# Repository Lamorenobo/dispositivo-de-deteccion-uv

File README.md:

# Dispositivo de detección uv
Nuestro dispositivo detecta la rediacion uv, y envia esta señal a una app en la cual dependiendo de el rango de  la radiacion se muestran las prevenciones que hay que tener para prevenir afectaciones por rayos UV
## Introducción
Nuestro proyecto consiste en un dispositivo capaz de detectar la radiacion UV, el cual envia unas señales al microcontrolador(ESP-32, programado en C), y dependiendo el rango de intensidad de radiacion UV, se encarga de prender o apagar unos leds en el dispositivo los cuales  indican la peligrosidad de la radiacion en ese momento especifico. Paralelamente a esto,mediante la conexion Bluetooth entre el esp 32 y el celular, se le indica al usario las prevenciones que deberia tomar de acuerdo al indice de radiación UV que este indicando el microcontrolador, todo esto a travez de una aplicacion programada en app inventor.
## ¿Porque?
Despues de realizar un analisis profundo al clima de la ciudad de Bogota, nos dimos cuenta que la radiacion UV durante el día, se mantiene en indices que se  consideran perjudicales para la piel.Ademas es importante mencionar que segun datos de la liga Colombiana contra el cancer y el INC Bogota es una de las ciudades con mas incidencia en casos de cancer de piel, y es aca donde nos dimos cuenta que estos dos datos estan correlacionados por lo cual nos pareció indispensable crear un dispositivo que avise en todo momento a los bogotanos sobre la radiacion UV que  se presenta al instante, y las precauciones que deberian tomar.
# Objetivo General
Desarrolar un Dispositivo que mediante la lectura del ESP-32 de los datos recogidos por el sensor UV, prenda determiando led indicando la intensidad de radiación UV en tiempo real y por conexión Wi-Fi enviar esta información a un aplicativo movil.
## Objetivos específicos
- Programar el microcontrolador y configurar la conectividad Wi-Fi
- Programar una aplicación que indique al usuario las precauciones que debería tomar, dependiendo la intensidad de radiacion UV en tiempo real
- Hacer en KICAD el Diseño de la placa (PCB) en la cual van a ir montados los componentes
- Hacer las respectivas pruebas del artefacto
- Documentar el proceso de creacion
# Materiales
- ESP-32
- Modulo de Carga MH18650
- Portabateria 18650
- Sensor UV Guva-s12sd
- 5 resistencias de 330 Ohmios
- 1 resistencia de 1KiloOhm
- Placa de Circuito (PCB)
- Materiales para soldar
- Bateria 9V
- 5 Leds
# Proceso Creativo
Empezariamos, como es debido en todo proceso de creacion tecnologico, con el diagrama de caja negra y el esquema del circuito:

## Diagrama de cajas negras

## Esquema del circuito 
A continuación presentamos el circuito  del dispositivo de detección UV elaborado en kicad.

## Programacion del ESP-32 (Micropython)
[codigo esp32 micropython (1).txt](https://github.com/Lamorenobo/dispositivo-de-deteccion-uv/files/13405623/codigo.esp32.micropython.1.txt)

## Version (Protoboard)
Tras tener la programacion del microcrontolador y el esquema del circuito, procedimos a pasarlo todo a una protoboard y comprobar el funcionamiento de todo el dispositivo<br>
 <br>
 <br>
<br>

En esas fotos se puede apreciar nuestra felicidad al percaarnos que el ESP-32 estaba haciendo su trabajo a la perfeccion, encendiendo y apagando Leds, dependiendo a la radiacion UV que fuera expuesto el SENSOR, ya solo faltaba empezar a crear la aplicacion
## Capitulo:PCB
Sin embargo debido a errores grupales no contabamos con que el proyecto debia realizarse sobre una PCB, por lo cual empezamos a documentarnos sobre el uso de la herramienta KICAD y las 
 librerias necesarias para armar el Esquema de la PCB para posteriormente mandarla a fabricar
###  Primera Version de la PCB:(Error)<br>
<br>
<br>

### PCB FINAL:

### Componentes en la PCB.....
Despues de tener Todos los materiales necesarios, nos vimos ante el reto de la soldadura puesto que ninguno tenia la experticia ni la tecnica para esta, sin embargo tras dedicarle bastante y con ayuda del profesor Johnny, logramos soldar todos los componenetes del dispositivo de manera correcta en la PCB:

#### Soldadura:

Dispositivo Final:

# Prueba ¿Final?:
Tras el armado del Dispositivo fisico procedimos a probarlo, y tras un primer fallo debido a un error de digitalizacion de un pin en el codigo, no obtuvimos el resultado esperado, sin embargo despues de corregir este error, obtuvimos lo que queriamos:

https://github.com/Lamorenobo/dispositivo-de-deteccion-uv/assets/142939223/29cb111f-80ca-4eb9-bf07-753b7d6bfc69

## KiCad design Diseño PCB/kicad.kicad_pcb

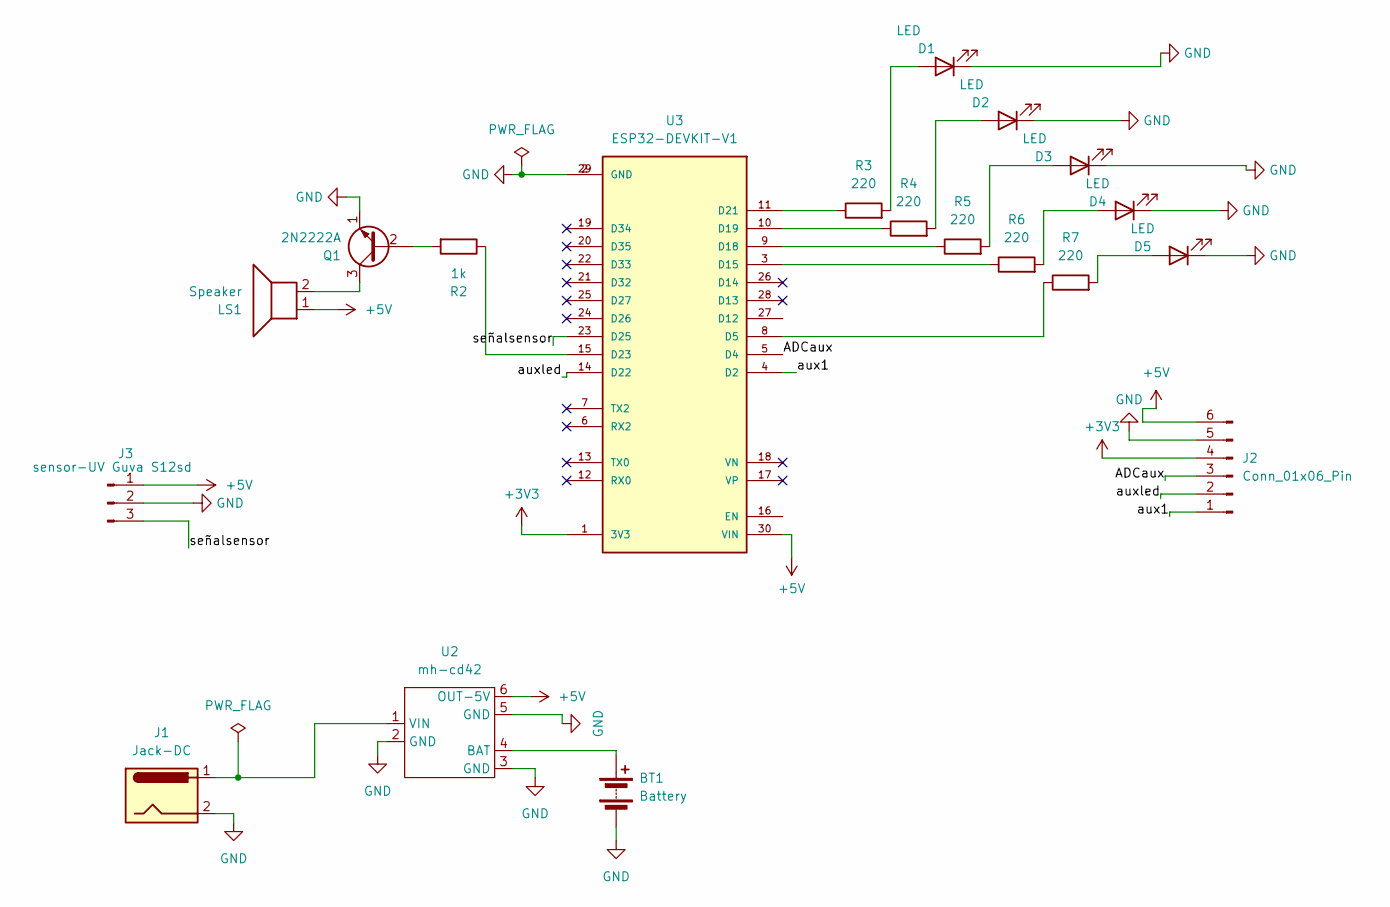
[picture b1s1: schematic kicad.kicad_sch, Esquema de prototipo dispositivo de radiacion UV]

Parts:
BT1: Battery; BatteryHolder_Keystone_1042_1x18650
D1, D2, D3, D4, D5: LED; LED_D4.0mm
J1: Jack-DC; BarrelJack_Horizontal
J2: Conn_01x06_Pin; PinSocket_1x06_P2.54mm_Vertical
J3: sensor-UV Guva S12sd; PinHeader_1x03_P2.54mm_Vertical
LS1: Speaker; MagneticBuzzer_ProSignal_ABI-009-RC
Q1: 2N2222A; TO-92
R2: 1k; R_Axial_DIN0207_L6.3mm_D2.5mm_P10.16mm_Horizontal
R3, R4, R5, R6, R7: 220; R_Axial_DIN0207_L6.3mm_D2.5mm_P10.16mm_Horizontal
U2: mh-cd42
U3: ESP32-DEVKIT-V1; MODULE_ESP32_DEVKIT_V1; PARTREV N/A

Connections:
+3V3: J2.4, U3.1 (3V3)
+5V: J2.6, J3.1, LS1.1, U2.6 (OUT-5V), U3.30 (VIN)
/ADCaux: J2.3, U3.5 (D4)
/aux1: J2.1, U3.4 (D2)
/auxled: J2.2, U3.14 (D22)
/señalsensor: J3.3, U3.23 (D25)
unnamed: BT1.1 (+), U2.4 (BAT)
unnamed: D1.2 (A), R3.2
unnamed: D2.2 (A), R4.2
unnamed: D3.2 (A), R5.2
unnamed: D4.2 (A), R6.2
unnamed: D5.2 (A), R7.2
unnamed: Q1.2 (B), R2.2
unnamed: LS1.2, Q1.3 (C)
unnamed: J1.1, U2.1 (VIN)
unnamed: R7.1, U3.8 (D5)
unnamed: R6.1, U3.3 (D15)
unnamed: R5.1, U3.9 (D18)
unnamed: R4.1, U3.10 (D19)
unnamed: R3.1, U3.11 (D21)
unnamed: R2.1, U3.15 (D23)

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
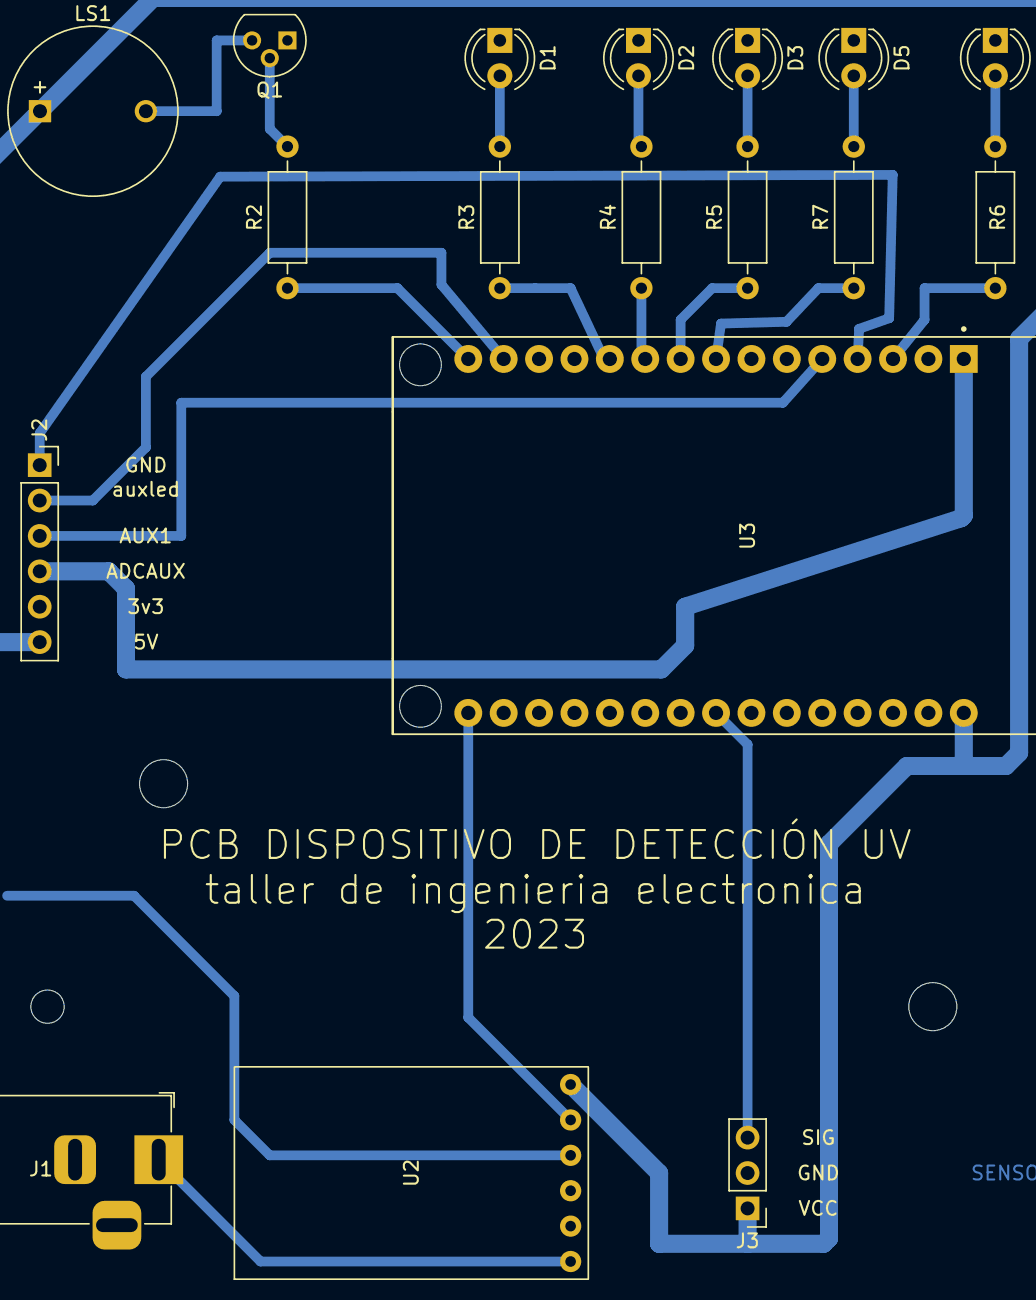
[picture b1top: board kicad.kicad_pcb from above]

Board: 2 copper layers, 19 parts (1 on the bottom side), 23 nets.
